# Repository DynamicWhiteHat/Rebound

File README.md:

# Rebound
Low-Cost Dysphagia Patch for Post-Stroke Patients

## Features:
### Core:
- ESP32S3 R8 SoC
- ADS1292 for surface electromyography (sEMG)
- AD5940 for bioimpedance analysis
- 16 MB flash with plenty of PSRAM
- Onboard battery charging
### Safety:
- 100K current limiting resistors on ADS1292
- 1K current limiting resistor and 15nF isolation capacitor on AD5940 current injection pin
- 470nF isolation capacitors on AD5940 read pins
- 2x TPD4E001 for ESD protection

## Image Gallery:
<table align="center">
  <tr>
    <td align="center">
      
    </td>
    <td align="center">
      
    </td>
  </tr>
  <tr>
    <td align="center" colspan="2">
      
    </td>
  </tr>
</table>

## About The Project
Created after learning about the dangers that post-stroke patients can face in my EMT class, Rebound is designed to assist those who may be struggling to recognize silent aspirations, ie, when food or liquid enters the airway and lungs instead of heading to the stomach. Traumatic brain injury, Parkinson's, and ALS can also cause individuals to experience this. Gone unrecognized, silent aspirations can lead to pneumonia and potenially respiratory arrest. Rebound is meant to be worn while eating or drinking, which will enable it to constantly scan for possible signs of a silent aspiration. In the event of one, the device will immediately alert the user to prevent further complications.

## Schematic And PCB

<table align="center">
  <tr>
    <td align="center" colspan="2">
      
    </td>
  </tr>
  <tr>
     <td align="center">
      
    </td>
    <td align="center">
      
    </td>
  </tr>
</table>

## Assembly
Once the PCB has been assembled, crimp and assemble the JST SH male connector with 10 wires. From left to right when viewed from above, the wires should be part of the 4-core strand, the 3-core strand, and another 3-core strand. Cut and strip the wires on the female electrode buttons and solder one to each of the wires not labeled GND. Then, place the PCB in the case, with the T-side pointing down. The case is meant to be worn on the backside of the neck, on a relatively flat and stiff portion to prevent the device from flexing. Plug in the JST connector and route the cables through the wire harness on the left side. Attach the RLD electrode on a bony prominence, such as the collarbone. All the following positions are based on the perspective of the user. The ADS+ electrode goes on the left half of the submental area (beneath the chin) when split vertically. The ADS- electrode goes on the right half of the submental area. The S+ electrode goes on the left sternocleidomastoid muscle. The F+ electrode goes between the S+ electrode and the Adam's Apple. The F- electrode goes on the other side of the Adam's Apple. Finally, the S- electrode goes on the right sternocleidomastoid muscle. The S+, F+, F-, and S- electrodes should all be in the same horizontal plane. Ensure none of the 7 electrodes overlap.

## How It Works
The combination of the ADS1292 and AD5940 ICs allows the device to recognize when a swallow is "off beat". Trained on data provided by a UCL study, the ADS1292 uses its sEMG abilities to monitor the activation of submental muscles that elevate the larynx to protect the airway during swallowing. Using a random forest algorithm, the device determines if the action performed was a swallow. By calculating the delta between the swallow and an object detected in the throat by the AD5940 and running it through a one-class SVM, whether or not a silent aspiration was performed can be determined.

## BOM

> [!NOTE]
> PEBA was selected for the 3D-printed case material as it is more flexible than JLC3DP's offering of TPU and biocompatible.

|Part                       |Quantity            |Price                |Link                                                                                |||  |                                          |
|---------------------------|--------------------|---------------------|------------------------------------------------------------------------------------|----------|---------|---------|--------------------------------------------------|
|PCB+Stencil                |1 Order             |$57.10               |JLCPCB Quote                                                                        |          |         |         |                                                  |
|PCB Parts                  |1 Order             |$92.88               |See Below                                                                           |          |         |         |                                                  |
|3D Printed Case            |1                   |$6.13                |JLC3DP Quote                                                                        |          |         |         |                                                  |
|Multi-Core Wire            |1x 3 Core, 1x 4 Core|$4.06                |https://www.aliexpress.us/item/2255800378204277.html                                |          |         |         |                                                  |
|Electrodes                 |1 Pack of 10        |$13.85               |https://www.amazon.com/TENS-Electrodes-Premium-Replacement-Discount/dp/B01BLYJEPK/  |          |         |         |                                                  |
|Shield Cap Holder          |1 Pack of 5         |$10.50               |https://www.aliexpress.us/item/3256808839294920.html                                |          |         |         |                                                  |
|Aluminum For Shield Cap    |1 Sheet             |$19.28               |https://www.aliexpress.us/item/3256807961227119.html                                |          |         |         |                                                  |
|JST SH Pins                |1 Box               |$4.36                |https://www.aliexpress.us/item/3256808432090471.html                                |          |         |         |                                                  |
|Electrode Buttons          |1 Pack of 10        |$3.21                |https://www.aliexpress.us/item/3256806634536037.html                                |          |         |         |                                                  |
|Velcro Straps              |1                   |$1.91                |https://www.aliexpress.us/item/3256808752475373.html                                |          |         |         |                                                  |
|LiPo Battery               |1                   |$9.00                |https://www.amazon.com/Battery-Rechargeable-Lithium-Polymer-Connector/dp/B09F9W7Z6J/|          |         |         |                                                  |
|                           |Total:              |$222.28              |                                                                                    |          |         |         |                                                  |
|LCSC                       |                    |                     |                                                                                    |          |         |         |                                                  |
|Description                |Quantity Needed     |Mrf#                 |Minimum Order Qty.                                                                  |Unit Price|Ext Price|LCSC#    |Link                                              |
|0.1uF                      |4                   |CL05B104KB54PNC      |100                                                                                 |0.0094    |0.94     |C307331  |https://www.lcsc.com/product-detail/C307331.html  |
|0.47uF                     |4                   |CL05A474KP5NNNC      |50                                                                                  |0.0211    |1.06     |C47339   |https://www.lcsc.com/product-detail/C47339.html   |
|1.5k                       |1                   |0402WGF1501TCE       |100                                                                                 |0.0057    |0.57     |C25867   |https://www.lcsc.com/product-detail/C25867.html   |
|1.5nF                      |1                   |GRM1555C1H152JA01D   |50                                                                                  |0.0278    |1.39     |C668348  |https://www.lcsc.com/product-detail/C668348.html  |
|100                        |1                   |0402WGF1000TCE       |100                                                                                 |0.0025    |0.25     |C25076   |https://www.lcsc.com/product-detail/C25076.html   |
|100K                       |3                   |RT0402BRE07100KL     |50                                                                                  |0.0259    |1.3      |C136979  |https://www.lcsc.com/product-detail/C136979.html  |
|100R                       |1                   |0402WGF1000TCE       |100                                                                                 |0.0025    |0.25     |C25076   |https://www.lcsc.com/product-detail/C25076.html   |
|100k                       |1                   |0402WGF1003TCE       |100                                                                                 |0.0076    |0.76     |C25741   |https://www.lcsc.com/product-detail/C25741.html   |
|100nF                      |11                  |CL05B104KB54PNC      |100                                                                                 |0.0094    |0.94     |C307331  |https://www.lcsc.com/product-detail/C307331.html  |
|10K                        |2                   |RC0402JR-0710KL      |100                                                                                 |0.0041    |0.41     |C60489   |https://www.lcsc.com/product-detail/C60489.html   |
|10k                        |2                   |RC0402JR-0710KL      |100                                                                                 |0.0041    |0.41     |C60489   |https://www.lcsc.com/product-detail/C60489.html   |
|10uF                       |3                   |CL05A106MQ5NUNC      |100                                                                                 |0.0257    |2.57     |C15525   |https://www.lcsc.com/product-detail/C15525.html   |
|12pF                       |2                   |CL05C120JB5NNNC      |100                                                                                 |0.0045    |0.45     |C26406   |https://www.lcsc.com/product-detail/C26406.html   |
|15nF                       |1                   |CC0402KRX7R9BB153    |100                                                                                 |0.0039    |0.39     |C114405  |https://www.lcsc.com/product-detail/C114405.html  |
|1K                         |1                   |4-1879208-9          |5                                                                                   |0.3163    |1.58     |C306197  |https://www.lcsc.com/product-detail/C306197.html  |
|1K                         |1                   |RT0402BRD071KL       |50                                                                                  |0.0271    |1.36     |C852624  |https://www.lcsc.com/product-detail/C852624.html  |
|1M                         |1                   |0402WGF1004TCE       |100                                                                                 |0.007     |0.7      |C26083   |https://www.lcsc.com/product-detail/C26083.html   |
|1uF                        |7                   |CL05A105KA5NQNC      |50                                                                                  |0.0162    |0.81     |C52923   |https://www.lcsc.com/product-detail/C52923.html   |
|2.2nH                      |1                   |LQG15HS2N2S02D       |50                                                                                  |0.0131    |0.66     |C86061   |https://www.lcsc.com/product-detail/C86061.html   |
|2.2nH                      |1                   |LQW15AN2N2C10D       |10                                                                                  |0.0628    |0.63     |C91240   |https://www.lcsc.com/product-detail/C91240.html   |
|24nH                       |1                   |MLG1005S24NHT000     |50                                                                                  |0.0078    |0.39     |C275275  |https://www.lcsc.com/product-detail/C275275.html  |
|2N7002                     |1                   |2N7002               |50                                                                                  |0.0176    |0.88     |C8545    |https://www.lcsc.com/product-detail/C8545.html    |
|3.3pF                      |2                   |GJM1555C1H3R3WB01D   |20                                                                                  |0.0374    |0.75     |C88892   |https://www.lcsc.com/product-detail/C88892.html   |
|3.9k                       |1                   |RC0402FR-073K9L      |100                                                                                 |0.0055    |0.55     |C131467  |https://www.lcsc.com/product-detail/C131467.html  |
|33                         |6                   |0402WGF330JTCE       |100                                                                                 |0.0034    |0.34     |C25105   |https://www.lcsc.com/product-detail/C25105.html   |
|4.7nF                      |2                   |GRM1555C1H472JE01D   |50                                                                                  |0.02      |1        |C1518204 |https://www.lcsc.com/product-detail/C1518204.html |
|4.7nF                      |1                   |0402B472K500NT       |100                                                                                 |0.0072    |0.72     |C1538    |https://www.lcsc.com/product-detail/C1538.html    |
|4.7uF                      |4                   |CL05A475MP5NRNC      |50                                                                                  |0.0233    |1.17     |C23733   |https://www.lcsc.com/product-detail/C23733.html   |
|470nF                      |3                   |GRM155R71C474KE01D   |20                                                                                  |0.0514    |1.03     |C471404  |https://www.lcsc.com/product-detail/C471404.html  |
|470pF                      |1                   |0402B471K500NT       |100                                                                                 |0.0075    |0.75     |C1537    |https://www.lcsc.com/product-detail/C1537.html    |
|47k                        |1                   |0402WGF4702TCE       |100                                                                                 |0.0063    |0.63     |C25792   |https://www.lcsc.com/product-detail/C25792.html   |
|47pF                       |2                   |0402CG470J500NT      |100                                                                                 |0.0152    |1.52     |C1567    |https://www.lcsc.com/product-detail/C1567.html    |
|5.1K                       |1                   |0402WGF5101TCE       |100                                                                                 |0.0057    |0.57     |C25905   |https://www.lcsc.com/product-detail/C25905.html   |
|5.1k                       |5                   |0402WGF5101TCE       |100                                                                                 |0.0057    |0.57     |C25905   |https://www.lcsc.com/product-detail/C25905.html   |
|750 mA                     |1                   |BSMD0603-075-6V      |10                                                                                  |0.0672    |0.67     |C914092  |https://www.lcsc.com/product-detail/C914092.html  |
|AD5941BCPZ                 |1                   |AD5941BCPZ           |1                                                                                   |20.615    |20.62    |C503573  |https://www.lcsc.com/product-detail/C503573.html  |
|ADS1292IRSMT               |1                   |ADS1292IRSMT         |1                                                                                   |9.4973    |9.5      |C89288   |https://www.lcsc.com/product-detail/C89288.html   |
|AP2112K-3.3                |1                   |AP2112K-3.3TRG1(MS)  |5                                                                                   |0.0748    |0.37     |C22365427|https://www.lcsc.com/product-detail/C22365427.html|
|BLM15PX121SN1D             |12                  |BLM15PX121SN1D       |50                                                                                  |0.0166    |0.83     |C88970   |https://www.lcsc.com/product-detail/C88970.html   |
|BQ24075RGT                 |1                   |BQ24075RGTR          |1                                                                                   |1.199     |1.2      |C15464   |https://www.lcsc.com/product-detail/C15464.html   |
|Conn_01x02_Socket          |1                   |S2B-PH-K-S(LF)(SN)   |20                                                                                  |0.0394    |0.79     |C173752  |https://www.lcsc.com/product-detail/C173752.html  |
|Conn_01x10                 |1                   |SM10B-SRSS-TB(LF)(SN)|1                                                                                   |0.4986    |0.5      |C160409  |https://www.lcsc.com/product-detail/C160409.html  |
|Crystal_GND24              |1                   |ECS-400-10-37-CKM-TR |1                                                                                   |0.9628    |0.96     |C5246840 |https://www.lcsc.com/product-detail/C5246840.html |
|D                          |1                   |BSD3C051V            |10                                                                                  |0.0661    |0.66     |C151996  |https://www.lcsc.com/product-detail/C151996.html  |
|ESP32-S3                   |1                   |ESP32-S3R8           |1                                                                                   |3.1722    |3.17     |C2913194 |https://www.lcsc.com/product-detail/C2913194.html |
|LED                        |1                   |LTST-C193TGKT-5A     |20                                                                                  |0.034     |0.68     |C12065   |https://www.lcsc.com/product-detail/C12065.html   |
|LED                        |1                   |KT-0603Y             |50                                                                                  |0.0107    |0.54     |C2287    |https://www.lcsc.com/product-detail/C2287.html    |
|MAX17048                   |1                   |MAX17048G+T10        |1                                                                                   |2.1836    |2.18     |C2682616 |https://www.lcsc.com/product-detail/C2682616.html |
|SW_Push                    |2                   |TS-1088-AR02016      |10                                                                                  |0.0529    |0.53     |C720477  |https://www.lcsc.com/product-detail/C720477.html  |
|SW_SPDT                    |1                   |SSSS811101           |5                                                                                   |0.149     |0.75     |C109335  |https://www.lcsc.com/product-detail/C109335.html  |
|TPD4E001DRSR.              |2                   |TPD4E001DRSR         |2                                                                                   |0.957     |1.91     |C1973310 |https://www.lcsc.com/product-detail/C1973310.html |
|TPS7A20xxxDBV              |1                   |TPS7A2033PDBVR       |5                                                                                   |0.2398    |1.2      |C2862740 |https://www.lcsc.com/product-detail/C2862740.html |
|USBLC6-2P6                 |1                   |USBLC6-2P6           |5                                                                                   |0.2787    |1.39     |C15999   |https://www.lcsc.com/product-detail/C15999.html   |
|USB_C_Receptacle_USB2.0_16P|1                   |TYPE-C-31-M-12       |5                                                                                   |0.1716    |0.86     |C165948  |https://www.lcsc.com/product-detail/C165948.html  |
|W25Q128JVP                 |1                   |W25Q128JVPIQ         |1                                                                                   |3.7478    |3.75     |C190862  |https://www.lcsc.com/product-detail/C190862.html  |
|JST SHR-10V-S-B            |1                   |SHR-10V-S-B          |5                                                                                   |0.1598    |$0.80    |C394370  |https://www.lcsc.com/product-detail/C394370.html  |
|                           |                    |                     |                                                                                    |Subtotal  |$82.16   |         |                                                  |
|                           |                    |                     |                                                                                    |Shipping  |$10.72   |         |                                                  |
|                           |                    |                     |                                                                                    |Total     |$92.88   |         |                                                  |

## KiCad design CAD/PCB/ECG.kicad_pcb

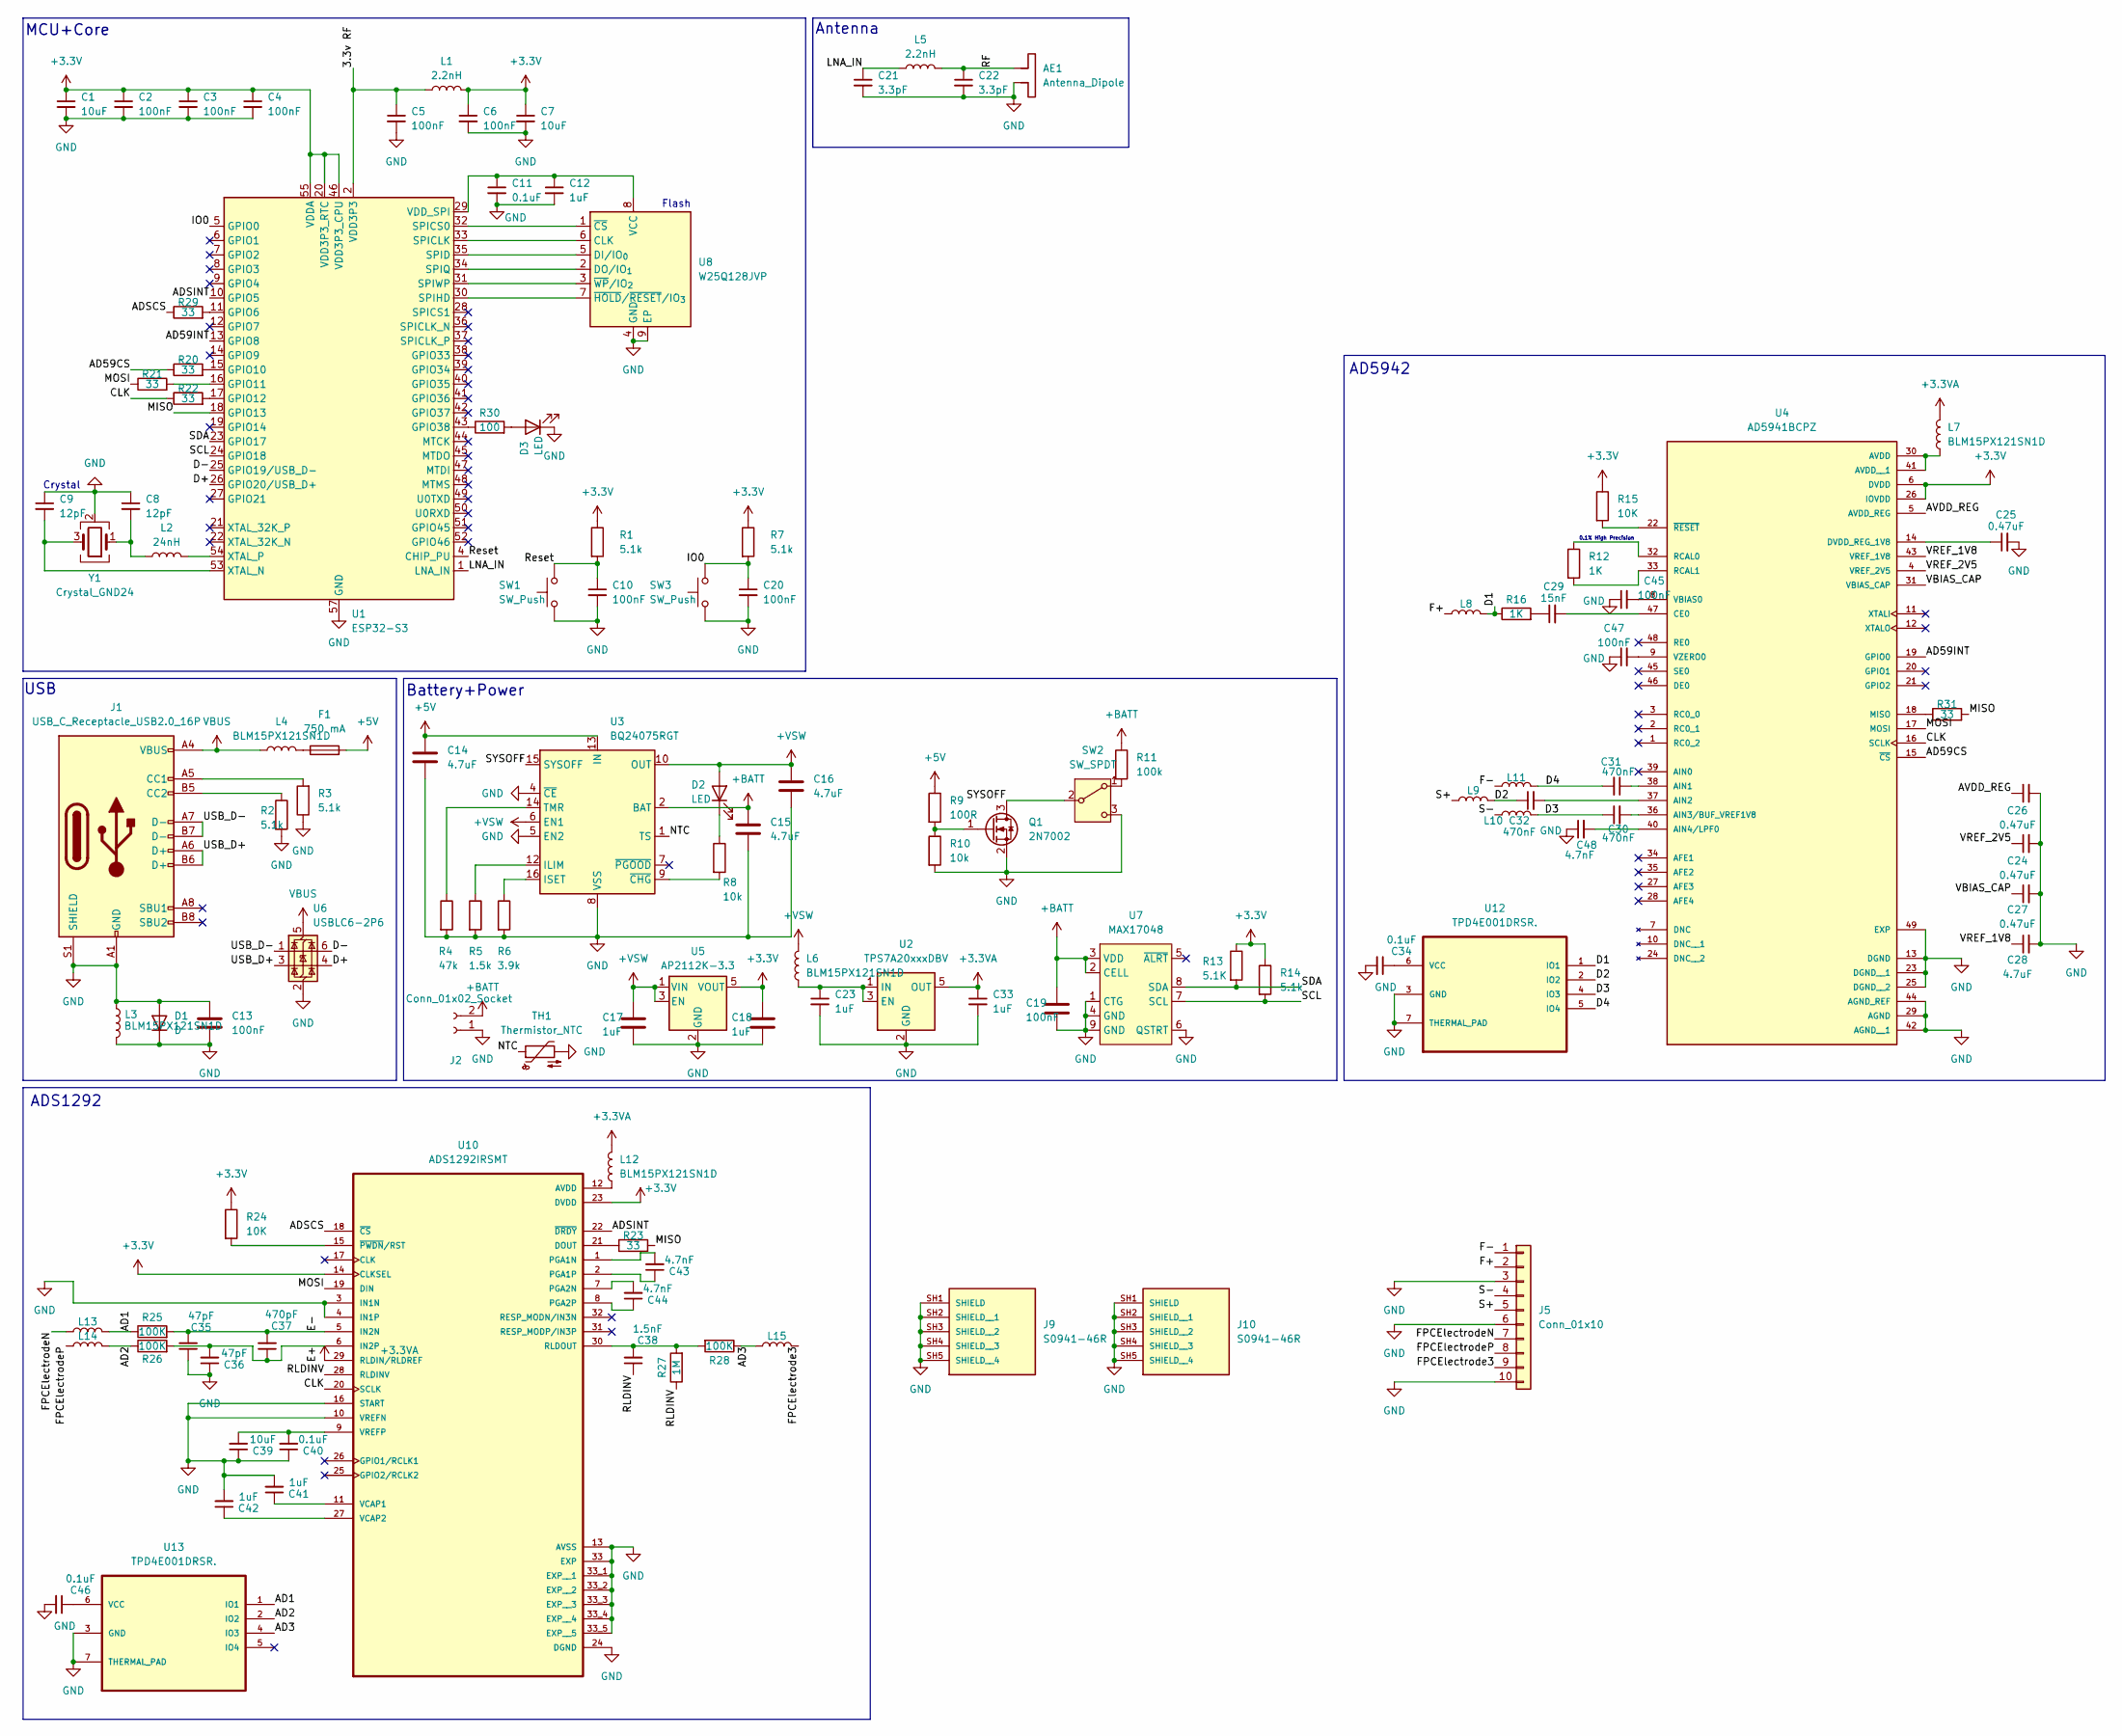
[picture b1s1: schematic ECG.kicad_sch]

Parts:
AE1: Antenna_Dipole; Texas_SWRA117D_2.4GHz_Left
C1, C7, C39: 10uF; C_0402_1005Metric
C2, C3, C4, C5, C6, C10, C13, C19, C20, C45, C47: 100nF; C_0402_1005Metric
C8, C9: 12pF; C_0402_1005Metric
C11, C34, C40, C46: 0.1uF; C_0402_1005Metric
C12, C17, C18, C23, C33, C41, C42: 1uF; C_0402_1005Metric
C14, C15, C16, C28: 4.7uF; C_0402_1005Metric
C21, C22: 3.3pF; C_0402_1005Metric
C24, C25, C26, C27: 0.47uF; C_0402_1005Metric
C29: 15nF; C_0402_1005Metric
C30, C31, C32: 470nF; C_0402_1005Metric
C35, C36: 47pF; C_0402_1005Metric
C37: 470pF; C_0402_1005Metric
C38: 1.5nF; C_0402_1005Metric
C43, C44, C48: 4.7nF; C_0402_1005Metric
D1: D; D_SOD-323
D2, D3: LED; LED_0603_1608Metric
F1: 750 mA; Fuse_0603_1608Metric
J1: USB_C_Receptacle_USB2.0_16P; USB_C_Receptacle_HRO_TYPE-C-31-M-12
J2: Conn_01x02_Socket; JST_PH_S2B-PH-K_1x02_P2.00mm_Horizontal
J5: Conn_01x10; JST_SH_SM10B-SRSS-TB_1x10-1MP_P1.00mm_Horizontal
J9, J10: S0941-46R; HARWIN_S0941-46R; PARTREV 4
L1, L5: 2.2nH; L_0402_1005Metric
L2: 24nH; L_0402_1005Metric
L3, L4, L6, L7, L8, L9, L10, L11, L12, L13, L14, L15: BLM15PX121SN1D; L_0402_1005Metric
Q1: 2N7002; SOT-23
R1, R2, R3, R7, R14: 5.1k; R_0402_1005Metric
R4: 47k; R_0402_1005Metric
R5: 1.5k; R_0402_1005Metric
R6: 3.9k; R_0402_1005Metric
R8, R10: 10k; R_0402_1005Metric
R9: 100R; R_0402_1005Metric
R11: 100k; R_0402_1005Metric
R12, R16: 1K; R_0402_1005Metric
R13: 5.1K; R_0402_1005Metric
R15, R24: 10K; R_0402_1005Metric
R20, R21, R22, R23, R29, R31: 33; R_0402_1005Metric
R25, R26, R28: 100K; R_0402_1005Metric
R27: 1M; R_0402_1005Metric
R30: 100; R_0402_1005Metric
SW1, SW3: SW_Push; SW_TS-1088-AR02016
SW2: SW_SPDT; SW_SSSS811101
TH1: Thermistor_NTC; PinHeader_1x02_P2.54mm_Vertical
U1: ESP32-S3; QFN-56-1EP_7x7mm_P0.4mm_EP4x4mm
U2: TPS7A20xxxDBV; SOT-23-5
U3: BQ24075RGT; VQFN-16-1EP_3x3mm_P0.5mm_EP1.6x1.6mm
U4: AD5941BCPZ; QFN50P700X700X80-49N; PARTREV B
U5: AP2112K-3.3; SOT-23-5
U6: USBLC6-2P6; SOT-666
U7: MAX17048; DFN-8-1EP_2x2mm_P0.5mm_EP0.8x1.6mm
U8: W25Q128JVP; WSON-8-1EP_6x5mm_P1.27mm_EP3.4x4.3mm
U10: ADS1292IRSMT; QFN40P400X400X100-33N
U12, U13: TPD4E001DRSR.; SON95P315X315X80-7N; MPN TPD4E001DRSR.
Y1: Crystal_GND24; Crystal_SMD_2016-4Pin_2.0x1.6mm

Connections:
+3.3V: C1.1, C2.1, C3.1, C4.1, C6.1, C7.1, C18.1, L1.2, R1.1, R7.1, R13.1, R14.1, R15.1, R24.1, U1.20 (VDD3P3_RTC), U1.46 (VDD3P3_CPU), U1.55 (VDDA), U1.56 (VDDA), U4.6 (DVDD), U4.26 (IOVDD), U5.5 (VOUT), U10.14 (CLKSEL), U10.23 (DVDD)
+3.3VA: C33.1, L7.2, L12.2, U2.5 (OUT), U10.29 (RLDIN/RLDREF)
+5V: C14.1, F1.2, R9.1, U3.13 (IN)
+BATT: C15.1, C19.1, J2.2, R11.1, U3.2 (BAT), U3.3 (BAT), U7.2 (CELL), U7.3 (VDD)
+VSW: C16.1, C17.1, D2.2 (A), L6.2, U3.6 (EN1), U3.10 (OUT), U3.11 (OUT), U5.1 (VIN), U5.3 (EN)
/3.3v RF: C5.1, L1.1, U1.2 (VDD3P3), U1.3 (VDD3P3)
/AD1: L13.2, R25.1, U13.1 (IO1)
/AD2: L14.2, R26.1, U13.2 (IO2)
/AD3: L15.1, R28.1, U13.4 (IO3)
/AD59CS: R20.1, U4.15 (~CS)
/AD59INT: U1.13 (GPIO8), U4.19 (GPIO0)
/ADSCS: R29.1, U10.18 (~CS)
/ADSINT: U1.10 (GPIO5), U10.22 (~DRDY)
/AVDD_REG: C26.1, U4.5 (AVDD_REG)
/CLK: R22.1, U4.16 (SCLK), U10.20 (SCLK)
/D1: L8.2, R16.1, U12.1 (IO1)
/D2: C32.1, L9.2, U12.2 (IO2)
/D3: C30.1, L10.2, U12.4 (IO3)
/D4: C31.2, L11.2, U12.5 (IO4)
/D+: U1.26 (GPIO20/USB_D+), U6.4 (I/O2)
/D-: U1.25 (GPIO19/USB_D-), U6.6 (I/O1)
/E+: C36.2, C37.1, R26.2, U10.6 (IN2P)
/E-: C35.2, C37.2, R25.2, U10.5 (IN2N)
/F+: J5.2, L8.1
/F-: J5.1, L11.1
/FPCElectrode3: J5.9, L15.2
/FPCElectrodeN: J5.7, L13.1
/FPCElectrodeP: J5.8, L14.1
/IO0: C20.1, R7.2, SW3.2, U1.5 (GPIO0)
/LNA_IN: C21.1, L5.1, U1.1 (LNA_IN)
/MISO: R23.2, R31.2, U1.18 (GPIO13)
/MOSI: R21.1, U4.17 (MOSI), U10.19 (DIN)
/NTC: TH1.1, U3.1 (TS)
/RF: AE1.1, C22.1, L5.2; also elsewhere on the board
/RLDINV: C38.1, R27.1, U10.28 (RLDINV)
/Reset: C10.1, R1.2, SW1.2, U1.4 (CHIP_PU)
/S+: J5.5, L9.1
/S-: J5.4, L10.1
/SCL: R14.2, U1.24 (GPIO18), U7.7 (SCL)
/SDA: R13.2, U1.23 (GPIO17), U7.8 (SDA)
/SYSOFF: Q1.3 (D), SW2.2 (B), U3.15 (SYSOFF)
/USB_D+: J1.A6 (D+), J1.B6 (D+), U6.3 (I/O2)
/USB_D-: J1.A7 (D-), J1.B7 (D-), U6.1 (I/O1)
/VBIAS_CAP: C27.1, U4.31 (VBIAS_CAP)
/VREF_1V8: C28.1, U4.43 (VREF_1V8)
/VREF_2V5: C24.1, U4.4 (VREF_2V5)
GND: AE1.2, C1.2, C2.2, C3.2, C4.2, C5.2, C6.2, C7.2, C8.1, C9.1, C10.2, C11.2, C12.2, C13.1, C13.2, C14.2, C15.2, C16.2, C17.2, C18.2, C19.2, C20.2, C21.2, C22.2, C23.2, C24.2, C25.2, C26.2, C27.2, C28.2, C33.2, C34.2, C35.1, C36.1, C39.1, C40.1, C41.2, C42.2, C45.1, C46.2, C47.1, C48.1, D1.1 (K), D1.2 (A), D3.1 (K), J1.A1 (GND), J1.A12 (GND), J1.B1 (GND), J1.B12 (GND), J1.S1 (SHIELD), J2.1, J5.3, J5.6, J5.10, J9.SH1 (SHIELD), J9.SH2 (SHIELD__1), J9.SH3 (SHIELD__2), J9.SH4 (SHIELD__3), J9.SH5 (SHIELD__4), J10.SH1 (SHIELD), J10.SH2 (SHIELD__1), J10.SH3 (SHIELD__2), J10.SH4 (SHIELD__3), J10.SH5 (SHIELD__4), L3.1, L3.2, Q1.2 (S), R2.2, R3.1, R4.2, R5.2, R6.2, R10.2, SW1.1, SW2.3 (C), SW3.1, TH1.2, U1.57 (GND), U2.2 (GND), U3.4 (~CE), U3.5 (EN2), U3.8 (VSS), U3.17 (VSS), U4.13 (DGND), U4.23 (DGND__1), U4.25 (DGND__2), U4.29 (AGND), U4.42 (AGND__1), U4.44 (AGND_REF), U4.49 (EXP), U5.2 (GND), U6.2 (GND), U7.1 (CTG), U7.4 (GND), U7.6 (QSTRT), U7.9 (GND), U8.4 (GND), U8.9 (EP), U10.3 (IN1N), U10.4 (IN1P), U10.10 (VREFN), U10.13 (AVSS), U10.16 (START), U10.24 (DGND), U10.33 (EXP), U10.33_1 (EXP__1), U10.33_2 (EXP__2), U10.33_3 (EXP__3), U10.33_4 (EXP__4), U10.33_5 (EXP__5), U12.3 (GND), U12.7 (THERMAL_PAD), U13.3 (GND), U13.7 (THERMAL_PAD), Y1.2 (G), Y1.4 (G); also elsewhere on the board
unnamed: C8.2, L2.1, Y1.1
unnamed: C29.1, R16.2
unnamed: D2.1 (K), R8.1
unnamed: D3.2 (A), R30.2
unnamed: F1.1, L4.2
unnamed: J1.A5 (CC1), R3.2
unnamed: J1.B5 (CC2), R2.1
unnamed: Q1.1 (G), R9.2, R10.1
unnamed: R11.2, SW2.1 (A)
unnamed: R29.2, U1.11 (GPIO6)
unnamed: R20.2, U1.15 (GPIO10)
unnamed: R21.2, U1.16 (GPIO11)
unnamed: R22.2, U1.17 (GPIO12)
unnamed: R30.1, U1.43 (GPIO38)
unnamed: U1.33 (SPICLK), U8.6 (CLK)
unnamed: U1.32 (SPICS0), U8.1 (~CS)
unnamed: U1.35 (SPID), U8.5 (DI/IO_{0})
unnamed: U1.30 (SPIHD), U8.7 (~HOLD/~RESET/IO_{3})
unnamed: U1.34 (SPIQ), U8.2 (DO/IO_{1})
unnamed: U1.31 (SPIWP), U8.3 (~WP/IO_{2})
unnamed: C11.1, C12.1, U1.29 (VDD_SPI), U8.8 (VCC)
unnamed: C9.2, U1.53 (XTAL_N), Y1.3
unnamed: L2.2, U1.54 (XTAL_P)
unnamed: C23.1, L6.1, U2.1 (IN), U2.3 (EN)
unnamed: R5.1, U3.12 (ILIM)
unnamed: R6.1, U3.16 (ISET)
unnamed: R4.1, U3.14 (TMR)
unnamed: R8.2, U3.9 (~CHG)
unnamed: C31.1, U4.38 (AIN1)
unnamed: C32.2, U4.37 (AIN2)
unnamed: C30.2, U4.36 (AIN3/BUF_VREF1V8)
unnamed: C48.2, U4.40 (AIN4/LPF0)
unnamed: L7.1, U4.30 (AVDD), U4.41 (AVDD__1)
unnamed: C29.2, U4.47 (CE0)
unnamed: C25.1, U4.14 (DVDD_REG_1V8)
unnamed: R31.1, U4.18 (MISO)
unnamed: R12.1, U4.32 (RCAL0)
unnamed: R12.2, U4.33 (RCAL1)
unnamed: C45.2, U4.8 (VBIAS0)
unnamed: C47.2, U4.9 (VZERO0)
unnamed: R15.2, U4.22 (~RESET)
unnamed: L12.1, U10.12 (AVDD)
unnamed: R23.1, U10.21 (DOUT)
unnamed: C43.2, U10.1 (PGA1N)
unnamed: C43.1, U10.2 (PGA1P)
unnamed: C44.2, U10.7 (PGA2N)
unnamed: C44.1, U10.8 (PGA2P)
unnamed: C38.2, R27.2, R28.2, U10.30 (RLDOUT)
unnamed: C41.1, U10.11 (VCAP1)
unnamed: C42.1, U10.27 (VCAP2)
unnamed: C39.2, C40.2, U10.9 (VREFP)
unnamed: R24.2, U10.15 (~PWDN/RST)
unnamed: C34.1, U12.6 (VCC)
unnamed: C46.1, U13.6 (VCC)
VBUS: J1.A4 (VBUS), J1.A9 (VBUS), J1.B4 (VBUS), J1.B9 (VBUS), L4.1, U6.5 (VBUS)

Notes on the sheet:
ADS1292
Crystal
Flash
AD5942
MCU+Core
0.1% High Precision
Battery+Power
Antenna
USB

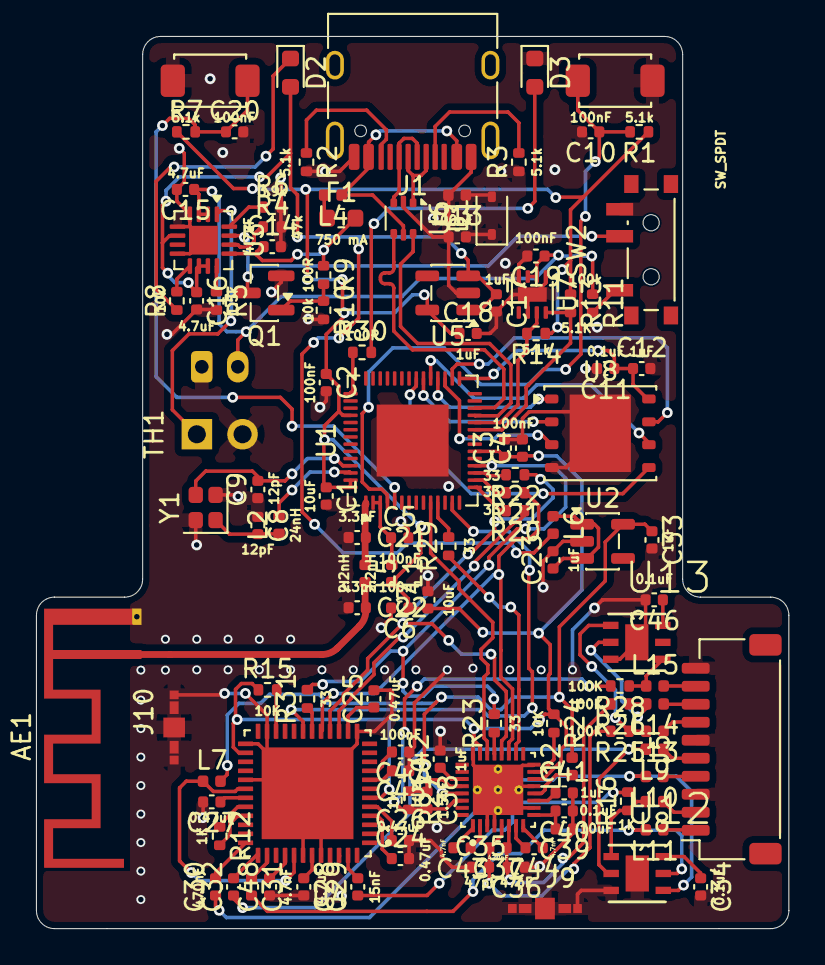
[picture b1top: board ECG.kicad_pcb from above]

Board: 4 copper layers, 41.8 x 49.6 mm, 119 parts (1 on the bottom side), 102 nets.

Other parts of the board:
AE1#2: Antenna_Dipole; Texas_SWRA117D_2.4GHz_Left

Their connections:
/RF: AE1#2.1; also elsewhere on the board
GND: AE1#2.2; also elsewhere on the board

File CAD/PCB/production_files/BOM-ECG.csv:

Comment,Designator,Footprint,LCSC,Quantity
0.1uF,"C11,C34,C40,C46",C_0402_1005Metric,C307331,4
0.47uF,"C24,C25,C26,C27",C_0402_1005Metric,C47339,4
1.5k,R5,R_0402_1005Metric,C25867,1
1.5nF,C38,C_0402_1005Metric,C668348,1
100K,"R25,R26,R28",R_0402_1005Metric,C136979,3
100R,"R30,R9",R_0402_1005Metric,C25076,2
100k,R11,R_0402_1005Metric,C25741,1
100nF,"C10,C13,C19,C2,C20,C3,C4,C45,C47,C5,C6",C_0402_1005Metric,C307331,11
10K,"R15,R24",R_0402_1005Metric,C60489,2
10k,"R10,R8",R_0402_1005Metric,C60489,2
10uF,"C1,C39,C7",C_0402_1005Metric,C15525,3
12pF,"C8,C9",C_0402_1005Metric,C26406,2
15nF,C29,C_0402_1005Metric,C114405,1
1K,R16,R_0402_1005Metric,C306197,1
1K,R12,R_0402_1005Metric,C852624,1
1M,R27,R_0402_1005Metric,C26083,1
1uF,"C12,C17,C18,C23,C33,C41,C42",C_0402_1005Metric,C52923,7
2.2nH,L1,L_0402_1005Metric,C86061,1
2.2nH,L5,L_0402_1005Metric,C91240,1
24nH,L2,L_0402_1005Metric,C275275,1
2N7002,Q1,SOT-23,C8545,1
3.3pF,"C21,C22",C_0402_1005Metric,C88892,2
3.9k,R6,R_0402_1005Metric,C131467,1
33,"R20,R21,R22,R23,R29,R31",R_0402_1005Metric,C25105,6
4.7nF,"C43,C44",C_0402_1005Metric,C1518204,2
4.7nF,C48,C_0402_1005Metric,C1538,1
4.7uF,"C14,C15,C16,C28",C_0402_1005Metric,C23733,4
470nF,"C30,C31,C32",C_0402_1005Metric,C471404,3
470pF,C37,C_0402_1005Metric,C1537,1
47k,R4,R_0402_1005Metric,C25792,1
47pF,"C35,C36",C_0402_1005Metric,C1567,2
5.1K,R13,R_0402_1005Metric,C25905,1
5.1k,"R1,R14,R2,R3,R7",R_0402_1005Metric,C25905,5
750 mA,F1,Fuse_0603_1608Metric,C914092,1
AD5941BCPZ,U4,QFN50P700X700X80-49N,C503573,1
ADS1292IRSMT,U10,QFN40P400X400X100-33N,C89288,1
AP2112K-3.3,U5,SOT-23-5,C22365427,1
BLM15PX121SN1D,"L10,L11,L12,L13,L14,L15,L3,L4,L6,L7,L8,L9",L_0402_1005Metric,C88970,12
BQ24075RGT,U3,VQFN-16-1EP_3x3mm_P0.5mm_EP1.6x1.6mm,C15464,1
Conn_01x02_Socket,J2,JST_PH_S2B-PH-K_1x02_P2.00mm_Horizontal,C173752,1
Conn_01x10,J5,JST_SH_SM10B-SRSS-TB_1x10-1MP_P1.00mm_Horizontal,C160409,1
Crystal_GND24,Y1,Crystal_SMD_2016-4Pin_2.0x1.6mm,C5246840,1
D,D1,D_SOD-323,C151996,1
ESP32-S3,U1,QFN-56-1EP_7x7mm_P0.4mm_EP4x4mm,C2913194,1
LED,D2,LED_0603_1608Metric,C12065,1
LED,D3,LED_0603_1608Metric,C2287,1
MAX17048,U7,DFN-8-1EP_2x2mm_P0.5mm_EP0.8x1.6mm,C2682616,1
SW_Push,"SW1,SW3",SW_TS-1088-AR02016,C720477,2
SW_SPDT,SW2,SW_SSSS811101,C109335,1
TPD4E001DRSR.,"U12,U13",SON95P315X315X80-7N,C1973310,2
TPS7A20xxxDBV,U2,SOT-23-5,C2862740,1
USBLC6-2P6,U6,SOT-666,C15999,1
USB_C_Receptacle_USB2.0_16P,J1,USB_C_Receptacle_HRO_TYPE-C-31-M-12,C165948,1
W25Q128JVP,U8,WSON-8-1EP_6x5mm_P1.27mm_EP3.4x4.3mm,C190862,1
Thermistor_NTC,TH1,PinHeader_1x02_P2.54mm_Vertical,,1
S0941-46R,J10,HARWIN_S0941-46R,,1
Antenna_Dipole,AE1,Texas_SWRA117D_2.4GHz_Left,,1
S0941-46R,J9,HARWIN_S0941-46R,,1
